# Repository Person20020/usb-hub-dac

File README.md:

# USB Hub / DAC

> [!NOTE]
> The design has a 22 ohm resistor across the DAC's crystal (I have no clue why I did that) but it should be 1M. It also worked fine just taking the 22 ohm resistor off and leaving it empty.

A simple USB hub with 3 USB C outputs and a built in DAC for a 3.5mm audio output. It uses a SL2.1a USB hub controller and a PCM2902 DAC. 

## PCB
The PCB is designed to be mounted into the case using four M2x6mm screws into the four printed standoffs that use heat set inserts. The mute button is mounted on the top of the PCB and the case has a built in flexing tab that is used as a push button.

Layout

Schematic

## Parts

| Part                                    | Quantity | LCSC #    | Price (each) | Total price      | Link                                                       |
| --------------------------------------- | -------- | --------- | ------------ | ---------------- | ---------------------------------------------------------- |
| PCM 2902                                | 1        | C2651869  | $15.0753     | $15.0753         | [Link](https://www.lcsc.com/product-detail/C2651869.html)  |
| SL2.1a                                  | 1        | C192893   | $0.2259      | $1.13 (5 MOQ)    | [Link](https://www.lcsc.com/product-detail/C192893.html)   |
| USBLC6-2SC6                             | 4        | C2827654  | $0.0387      | $0.39 (10 MOQ)   | [Link](https://www.lcsc.com/product-detail/C2827654.html)  |
| PJ-320D 3.5mm TRRS Jack                 | 1        | C431535   | $0.0483      | $0.48 (10 MOQ)   | [Link](https://www.lcsc.com/product-detail/C431535.html)   |
| GCT_USB4110 USB C Port                  | 4        | C5143397  | $1.8037      | $7.21            | [Link](https://www.lcsc.com/product-detail/C5143397.html)  |
| 56k ohm 0805 Resistors                  | 6        | C2907336  | $0.0014      | $0.14 (100 MOQ)  | [Link](https://www.lcsc.com/product-detail/C2907336.html)  |
| 5.1k ohm 0805 Resistors                 | 2        | C2930296  | $0.0013      | $0.13 (100 MOQ)  | [Link](https://www.lcsc.com/product-detail/C2930296.html)  |
| 1.5k ohm 0805 Resistors                 | 1        | C2907216  | $0.0017      | $0.17 (100 MOQ)  | [Link](https://www.lcsc.com/product-detail/C2907216.html)  |
| 2.2 ohm 0805 Resistors                  | 1        | C2933402  | $0.0023      | $0.23 (100 MOQ)  | [Link](https://www.lcsc.com/product-detail/C2933402.html)  |
| 22 ohm 0805 Resistors                   | 3        | C2907310  | $0.0014      | $0.014 (100 MOQ) | [Link](https://www.lcsc.com/product-detail/C2907310.html)  |
| 10k ohm 0805 Resistors                  | 3        | C2930231  | $0.0012      | $0.012 (100 MOQ) | [Link](https://www.lcsc.com/product-detail/C2930231.html)  |
| 10uF Radial D4mm L8mm P1.5mm Capacitors | 4        | C36914040 | $0.0402      | $0.2 (5 MOQ)     | [Link](https://www.lcsc.com/product-detail/C36914040.html) |
| 10uF 0805 Capacitors                    | 6        | C1713     | $0.0088      | $0.18 (20 MOQ)   | [Link](https://www.lcsc.com/product-detail/C1713.html)     |
| 1uF 0805 Capacitors                     | 3        | C28323    | $0.0092      | $0.18 (20 MOQ)   | [Link](https://www.lcsc.com/product-detail/C28323.html)    |
| 10pF 0805 Capacitors                    | 2        | C41361255 | $0.0045      | $0.45 (100 MOQ)  | [Link](https://www.lcsc.com/product-detail/C41361255.html) |
| 6mm Push Button                         | 1        | C42416249 | $0.0196      | $0.39 (20 MOQ)   | [Link](https://www.lcsc.com/product-detail/C42416249.html) |
| 12 MHz Crystal                          | 2        | C16369    | $0.0834      | $0.42 (5 MOQ)    | [Link](https://www.lcsc.com/product-detail/C16369.html)    |

Total cost: \~$26.80 + PCB (\~$2)

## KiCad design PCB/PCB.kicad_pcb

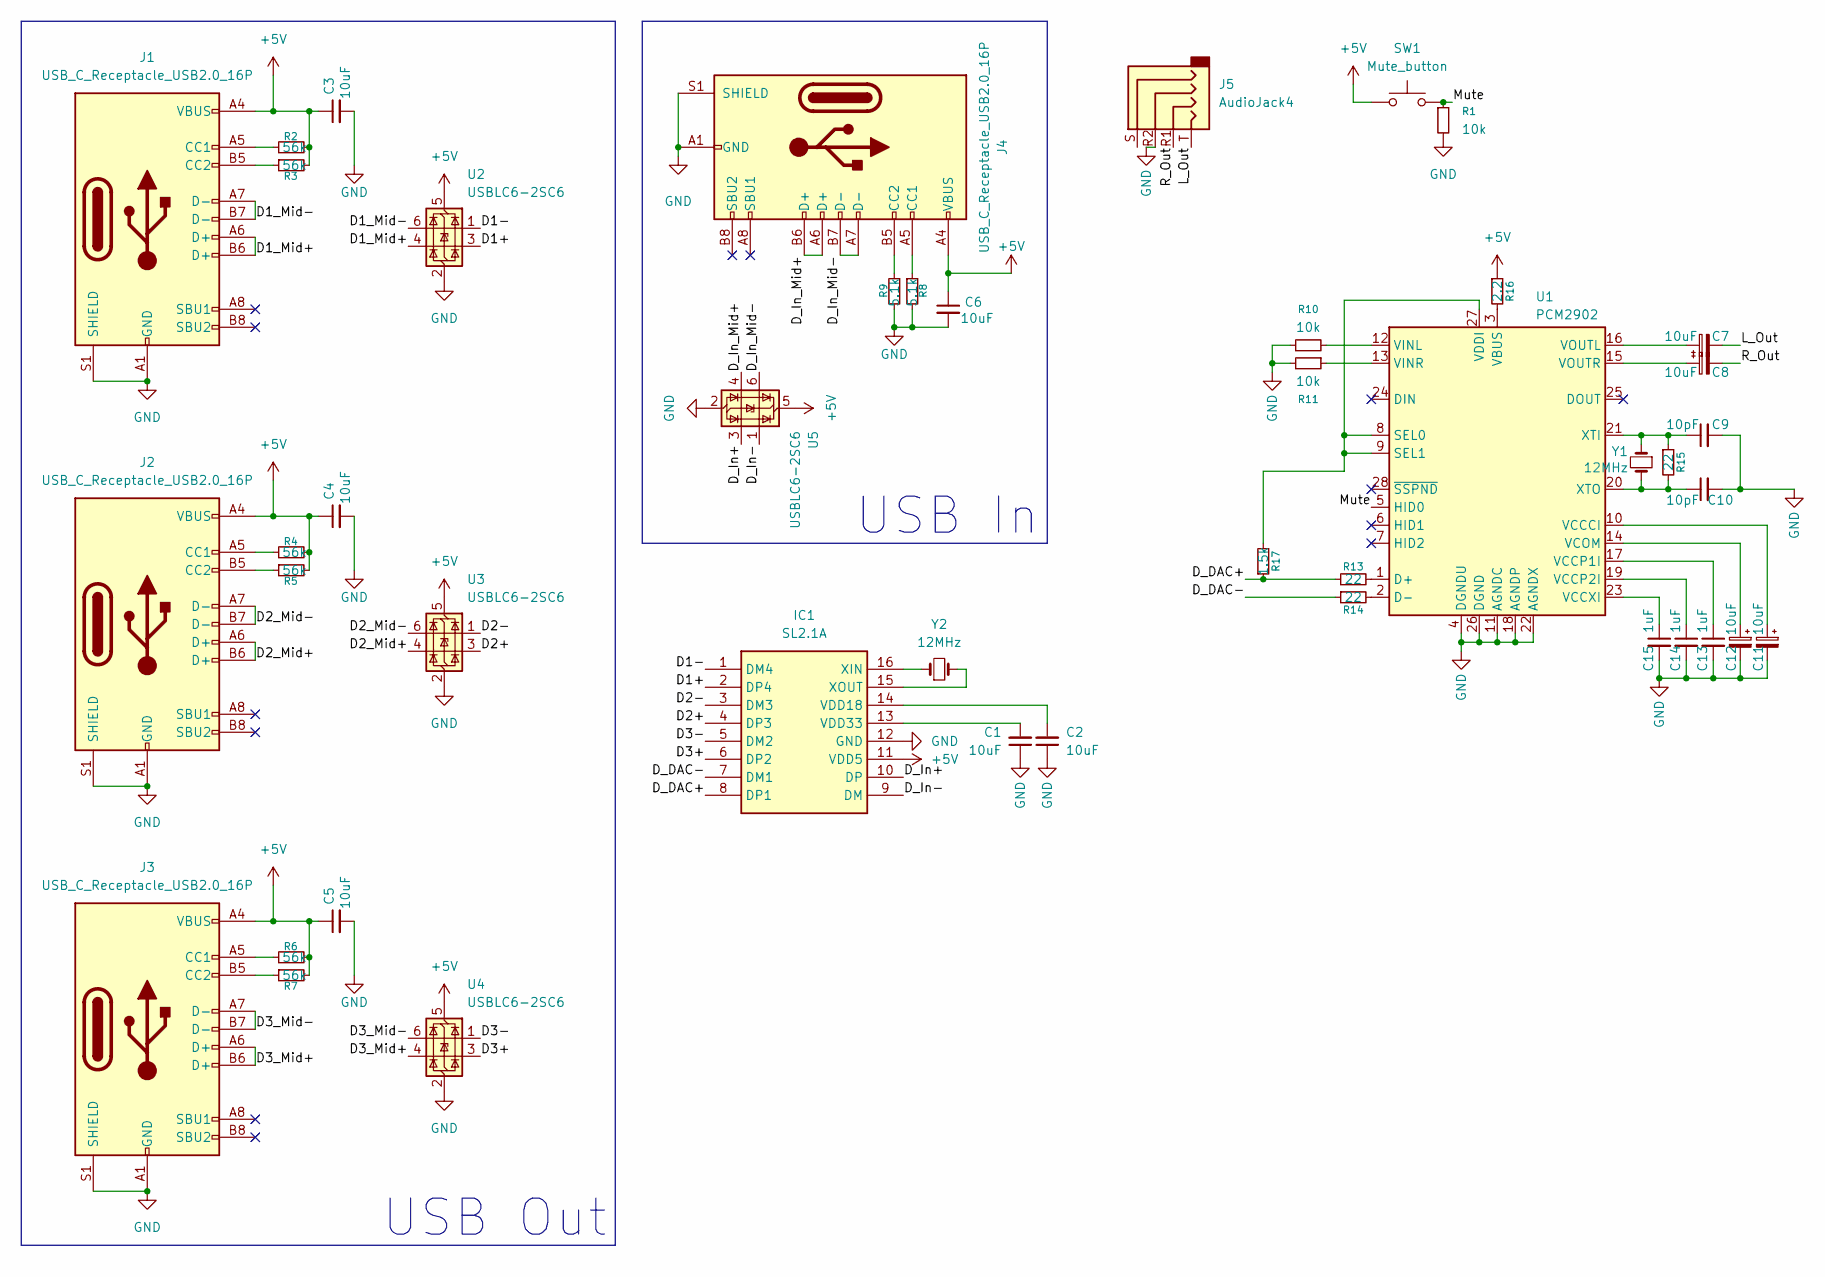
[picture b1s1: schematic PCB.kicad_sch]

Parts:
C1, C2, C3, C4, C5, C6: 10uF; C_0805_2012Metric_Pad1.18x1.45mm_HandSolder
C7, C8, C11, C12: 10uF; C_Radial_D4.0mm_H7.0mm_P1.50mm
C9, C10: 10pF; C_0805_2012Metric_Pad1.18x1.45mm_HandSolder
C13, C14, C15: 1uF; C_0805_2012Metric_Pad1.18x1.45mm_HandSolder
IC1: SL2.1A; STC_SOP-16_3.9x9.9mm_P1.27mm; Manufacturer_Part_Number SL2.1A
J1, J2, J3, J4: USB_C_Receptacle_USB2.0_16P; USB_C_Receptacle_GCT_USB4110
J5: AudioJack4; Jack_3.5mm_PJ320D_Horizontal
R1, R10, R11: 10k; R_0805_2012Metric_Pad1.20x1.40mm_HandSolder
R2, R3, R4, R5, R6, R7: 56k; R_0805_2012Metric_Pad1.20x1.40mm_HandSolder
R8, R9: 5.1k; R_0805_2012Metric_Pad1.20x1.40mm_HandSolder
R13, R14, R15: 22; R_0805_2012Metric_Pad1.20x1.40mm_HandSolder
R16: 2.2; R_0805_2012Metric_Pad1.20x1.40mm_HandSolder
R17: 1.5k; R_0805_2012Metric_Pad1.20x1.40mm_HandSolder
SW1: Mute_button; SW_PUSH_6mm_H7.3mm
U1: PCM2902; SSOP-28_5.3x10.2mm_P0.65mm
U2, U3, U4, U5: USBLC6-2SC6; SOT-23-6
Y1, Y2: 12MHz; Crystal_HC49-4H_Vertical

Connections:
+5V: C3.1, C4.1, C5.1, C6.1, IC1.11 (VDD5), J1.A4 (VBUS), J1.A9 (VBUS), J1.B4 (VBUS), J1.B9 (VBUS), J2.A4 (VBUS), J2.A9 (VBUS), J2.B4 (VBUS), J2.B9 (VBUS), J3.A4 (VBUS), J3.A9 (VBUS), J3.B4 (VBUS), J3.B9 (VBUS), J4.A4 (VBUS), J4.A9 (VBUS), J4.B4 (VBUS), J4.B9 (VBUS), R2.2, R3.2, R4.2, R5.2, R6.2, R7.2, R16.1, SW1.1, U2.5 (VBUS), U3.5 (VBUS), U4.5 (VBUS), U5.5 (VBUS)
/D1+: IC1.2 (DP4), U2.3 (I/O2)
/D1-: IC1.1 (DM4), U2.1 (I/O1)
/D1_Mid+: J1.A6 (D+), J1.B6 (D+), U2.4 (I/O2)
/D1_Mid-: J1.A7 (D-), J1.B7 (D-), U2.6 (I/O1)
/D2+: IC1.4 (DP3), U3.3 (I/O2)
/D2-: IC1.3 (DM3), U3.1 (I/O1)
/D2_Mid+: J2.A6 (D+), J2.B6 (D+), U3.4 (I/O2)
/D2_Mid-: J2.A7 (D-), J2.B7 (D-), U3.6 (I/O1)
/D3+: IC1.6 (DP2), U4.3 (I/O2)
/D3-: IC1.5 (DM2), U4.1 (I/O1)
/D3_Mid+: J3.A6 (D+), J3.B6 (D+), U4.4 (I/O2)
/D3_Mid-: J3.A7 (D-), J3.B7 (D-), U4.6 (I/O1)
/D_DAC+: IC1.8 (DP1), R13.1, R17.1
/D_DAC-: IC1.7 (DM1), R14.1
/D_In+: IC1.10 (DP), U5.3 (I/O2)
/D_In-: IC1.9 (DM), U5.1 (I/O1)
/D_In_Mid+: J4.A6 (D+), J4.B6 (D+), U5.4 (I/O2)
/D_In_Mid-: J4.A7 (D-), J4.B7 (D-), U5.6 (I/O1)
/L_Out: C7.2, J5.T
/Mute: R1.1, SW1.2, U1.5 (HID0)
/R_Out: C8.2, J5.R1
GND: C1.1, C2.1, C3.2, C4.2, C5.2, C6.2, C9.2, C10.2, C11.2, C12.2, C13.2, C14.2, C15.2, IC1.12 (GND), J1.A1 (GND), J1.A12 (GND), J1.B1 (GND), J1.B12 (GND), J1.S1 (SHIELD), J2.A1 (GND), J2.A12 (GND), J2.B1 (GND), J2.B12 (GND), J2.S1 (SHIELD), J3.A1 (GND), J3.A12 (GND), J3.B1 (GND), J3.B12 (GND), J3.S1 (SHIELD), J4.A1 (GND), J4.A12 (GND), J4.B1 (GND), J4.B12 (GND), J4.S1 (SHIELD), J5.R2, R1.2, R8.2, R9.2, R10.1, R11.2, U1.4 (DGNDU), U1.11 (AGNDC), U1.18 (AGNDP), U1.22 (AGNDX), U1.26 (DGND), U2.2 (GND), U3.2 (GND), U4.2 (GND), U5.2 (GND)
unnamed: C2.2, IC1.14 (VDD18)
unnamed: C1.2, IC1.13 (VDD33)
unnamed: IC1.16 (XIN), Y2.1
unnamed: IC1.15 (XOUT), Y2.2
unnamed: J1.A5 (CC1), R2.1
unnamed: J1.B5 (CC2), R3.1
unnamed: J2.A5 (CC1), R4.1
unnamed: J2.B5 (CC2), R5.1
unnamed: J3.A5 (CC1), R6.1
unnamed: J3.B5 (CC2), R7.1
unnamed: J4.A5 (CC1), R8.1
unnamed: J4.B5 (CC2), R9.1
unnamed: R13.2, U1.1 (D+)
unnamed: R14.2, U1.2 (D-)
unnamed: R17.2, U1.8 (SEL0), U1.9 (SEL1), U1.27 (VDDI)
unnamed: R16.2, U1.3 (VBUS)
unnamed: C11.1, U1.10 (VCCCI)
unnamed: C13.1, U1.17 (VCCP1I)
unnamed: C14.1, U1.19 (VCCP2I)
unnamed: C15.1, U1.23 (VCCXI)
unnamed: C12.1, U1.14 (VCOM)
unnamed: R10.2, U1.12 (VINL)
unnamed: R11.1, U1.13 (VINR)
unnamed: C7.1, U1.16 (VOUTL)
unnamed: C8.1, U1.15 (VOUTR)
unnamed: C9.1, R15.1, U1.21 (XTI), Y1.1
unnamed: C10.1, R15.2, U1.20 (XTO), Y1.2

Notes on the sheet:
USB In
USB Out

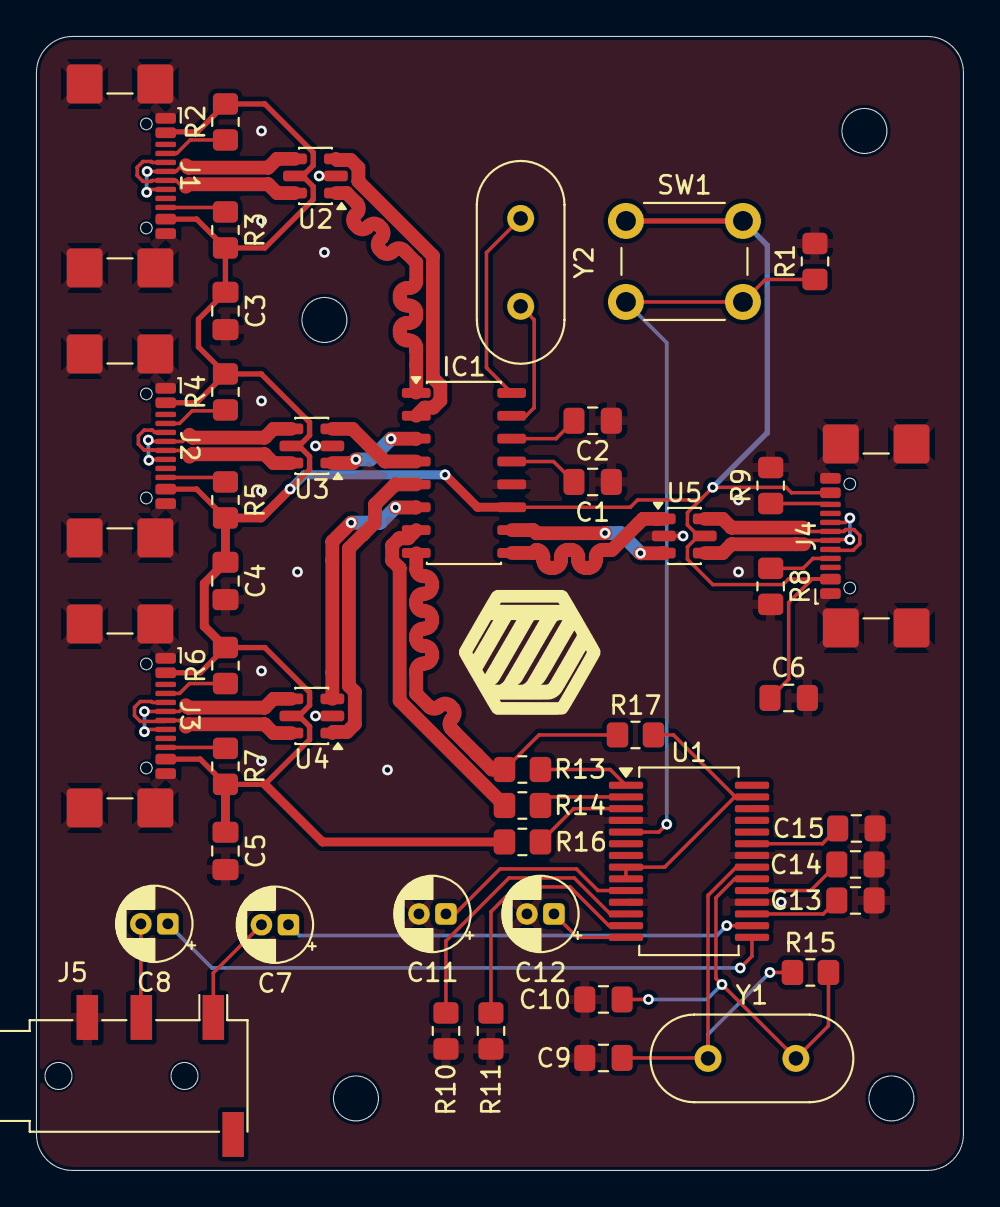
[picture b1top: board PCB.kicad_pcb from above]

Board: 2 copper layers, 51.5 x 63.0 mm, 45 parts (0 on the bottom side), 50 nets.

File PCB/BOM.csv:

"Id";"Designator";"Footprint";"Quantity";"Designation";"Supplier and ref";
1;"U2,U5,U4,U3";"SOT-23-6";4;"USBLC6-2SC6";;;
2;"J4,J3,J1,J2";"USB_C_Receptacle_GCT_USB4110";4;"USB_C_Receptacle_USB2.0_16P";;;
3;"R4,R6,R2,R3,R7,R5";"R_0805_2012Metric_Pad1.20x1.40mm_HandSolder";6;"56k";;;
4;"C12,C7,C8,C11";"CP_Radial_D4.0mm_P1.50mm";4;"10uF";;;
5;"C5,C6,C1,C4,C3,C2";"C_0805_2012Metric_Pad1.18x1.45mm_HandSolder";6;"10uF";;;
6;"U1";"SSOP-28_5.3x10.2mm_P0.65mm";1;"PCM2902";;;
7;"R1,R10,R11";"R_0805_2012Metric_Pad1.20x1.40mm_HandSolder";3;"10k";;;
8;"C9,C10";"C_0805_2012Metric_Pad1.18x1.45mm_HandSolder";2;"10pF";;;
9;"R17";"R_0805_2012Metric_Pad1.20x1.40mm_HandSolder";1;"1.5k";;;
10;"J5";"Jack_3.5mm_PJ320D_Horizontal";1;"AudioJack4";;;
11;"R8,R9";"R_0805_2012Metric_Pad1.20x1.40mm_HandSolder";2;"5.1k";;;
12;"R16";"R_0805_2012Metric_Pad1.20x1.40mm_HandSolder";1;"2.2";;;
13;"R13,R15,R14";"R_0805_2012Metric_Pad1.20x1.40mm_HandSolder";3;"22";;;
14;"C15,C13,C14";"C_0805_2012Metric_Pad1.18x1.45mm_HandSolder";3;"1uF";;;
15;"SW1";"SW_PUSH_6mm_H7.3mm";1;"Mute_button";;;
16;"IC1";"STC_SOP-16_3.9x9.9mm_P1.27mm";1;"SL2.1A";;;
17;"Y2,Y1";"Crystal_HC49-4H_Vertical";2;"12MHz";;;

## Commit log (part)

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2025-12-03 Wire USB part of schematic and start DAC.
2025-12-05 fixed schematic and routed usb hub
2025-12-06 finish pcb and generate gerbers
2025-12-08 add bom.csv and parts list to readme
2025-12-10 add case and add description to readme
2025-12-10 Add images
2025-12-10 Add total cost to readme
2025-12-12 add silkscreen and update gerbers
